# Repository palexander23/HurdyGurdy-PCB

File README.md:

# Electronic Hurdy Gurdy PCB

This repository contains PCB design files, that will go towards the eventual creation of an electronic Hurdy Gurdy.

This is a stand-in README that will likely be rewritten once the project starts taking off.

I do not intend this project to be seen widely, it's just a place for me to keep stuff.

This project was heavily inspired by the [Digi-Gurdy](https://hackaday.io/project/165251-the-digi-gurdy-and-diginerdygurdy) and much of the mechanical design for my instrument will likely be drawn from there.

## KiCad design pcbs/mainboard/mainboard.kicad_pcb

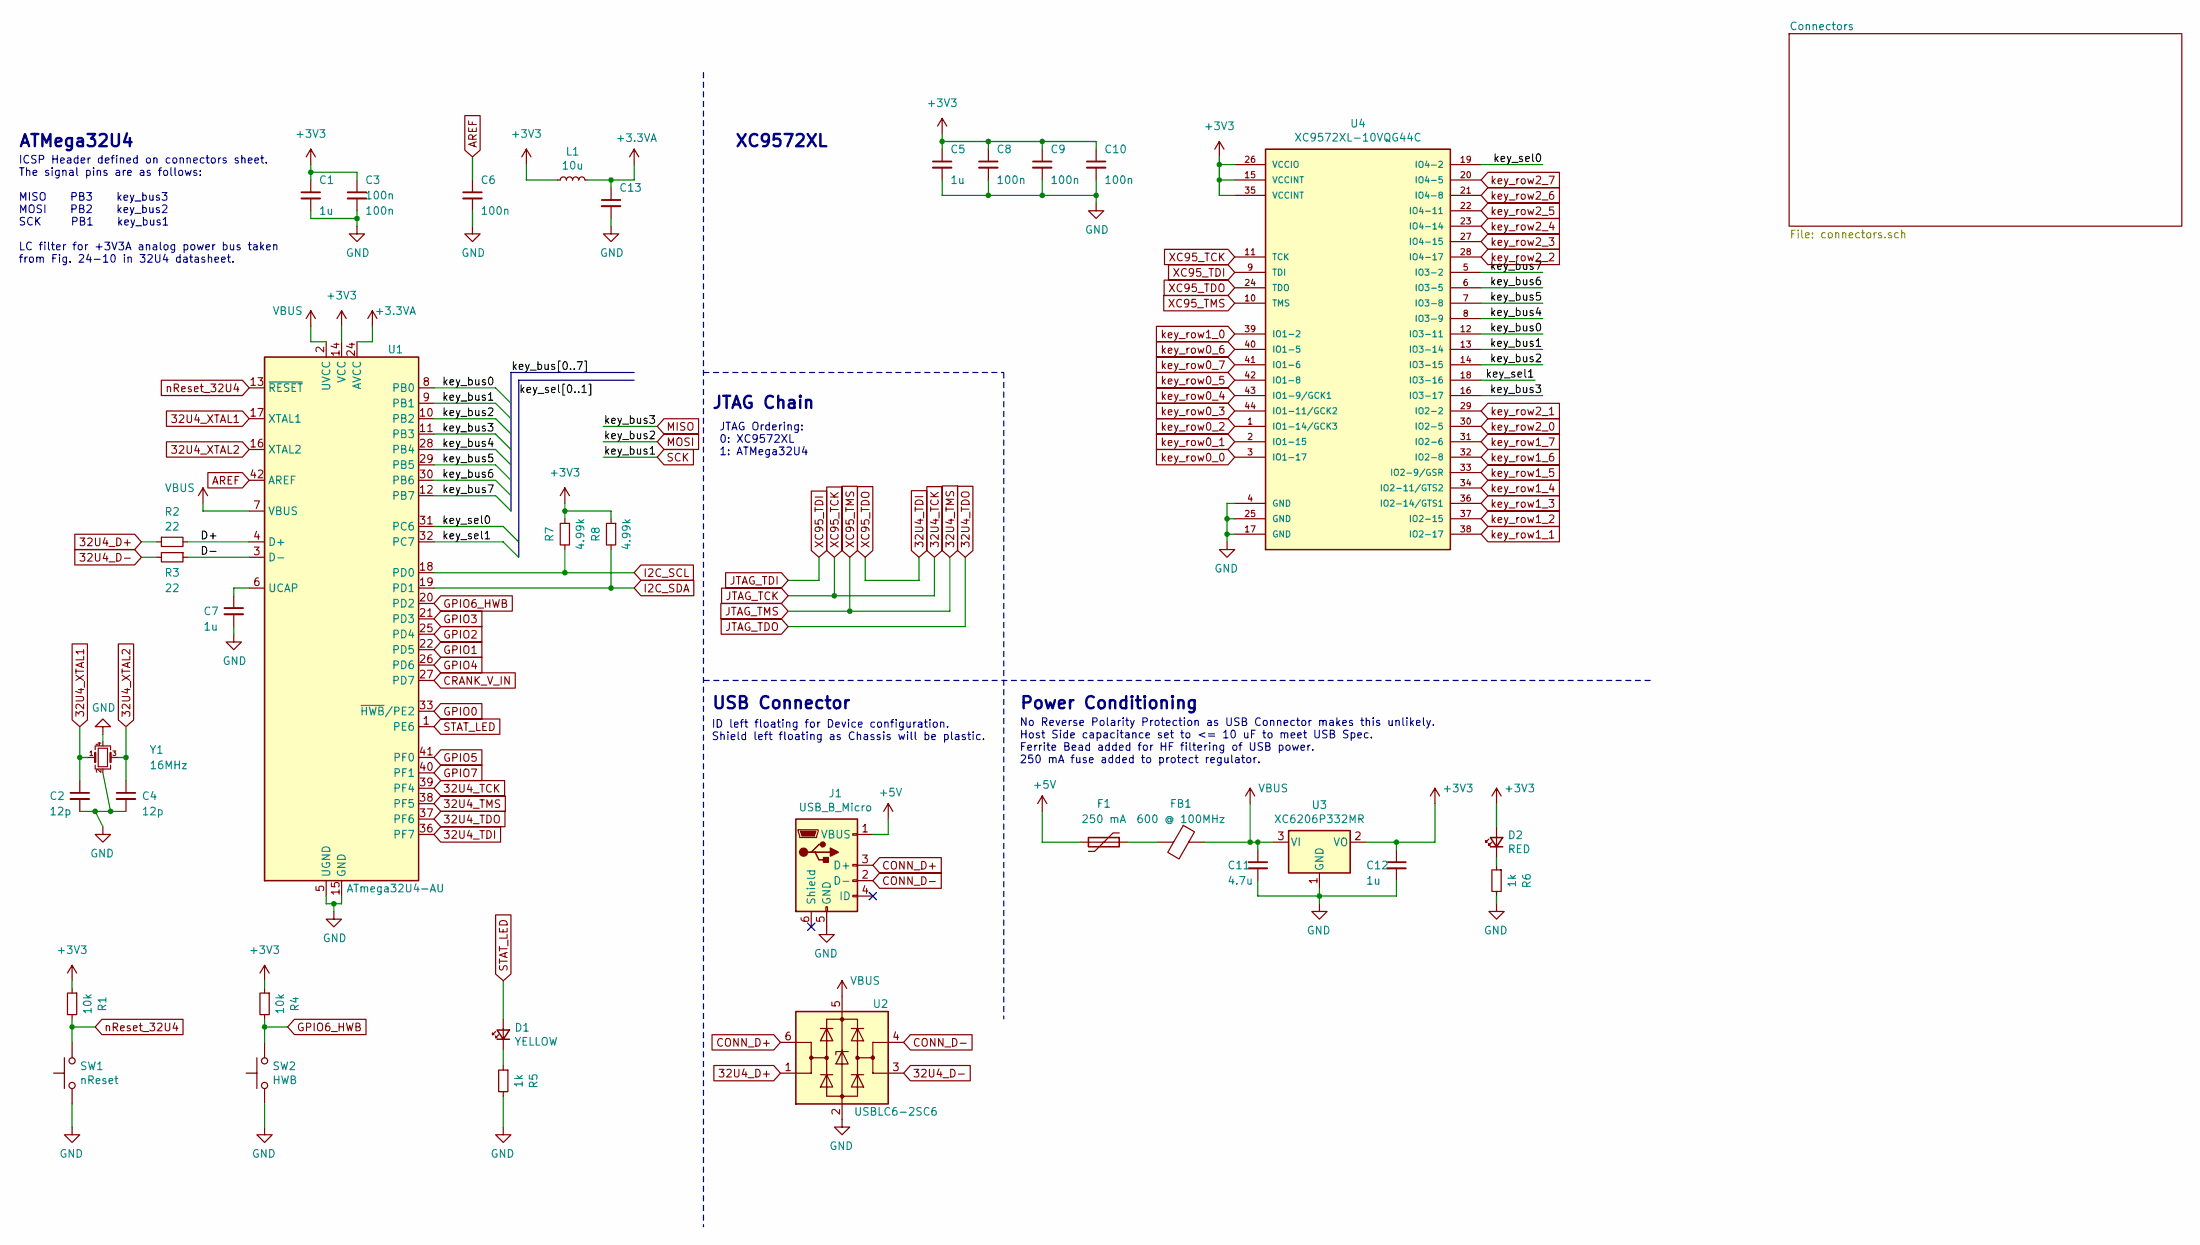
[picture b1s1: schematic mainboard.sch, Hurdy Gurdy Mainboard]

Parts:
C1, C5, C7, C12: 1u; C_0603_1608Metric; JLCPCB Part # C15849
C2, C4: 12p; C_0603_1608Metric; JLCPCB Part # C38523
C3, C6, C8, C9, C10, C13: 100n; C_0603_1608Metric; JLCPCB Part # C14663
C11: 4.7u; C_0603_1608Metric; JLCPCB Part # C19666
D1: YELLOW; LED_0603_1608Metric; JLCPCB Part # C72038
D2: RED; LED_0603_1608Metric; JLCPCB Part # C2286
F1: 250 mA; Fuse_1206_3216Metric; JLCPCB Part # C369154
FB1: 600 @ 100MHz; L_0805_2012Metric; JLCPCB Part # C1017
J1: USB_B_Micro; USB_Micro-B_Amphenol_10103594-0001LF_Horizontal
L1: 10u; L_1206_3216Metric; JLCPCB Part # C1051
R1, R4: 10k; R_0603_1608Metric; JLCPCB Part # C25804
R2, R3: 22; R_0603_1608Metric; JLCPCB Part # C23345
R5, R6: 1k; R_0603_1608Metric; JLCPCB Part # C21190
R7, R8: 4.99k; R_0603_1608Metric; JLCPCB Part # C23046
SW1: nReset; SW_PUSH_6mm
SW2: HWB; SW_PUSH_6mm
U1: ATmega32U4-AU; TQFP-44_10x10mm_P0.8mm; JLCPCB Part # C44854
U2: USBLC6-2SC6; SOT-23-6; JLCPCB Part # C2827654
U3: XC6206P332MR; SOT-23; JLCPCB Part # C5446
U4: XC9572XL-10VQG44C; VQFP-44; JLCPCB Part # C569042
Y1: 16MHz; Crystal_SMD_3225-4Pin_3.2x2.5mm; JLCPCB Part # C13738

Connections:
32U4_D+: R2.1, U2.1 (I/O1)
32U4_D-: R3.2, U2.3 (I/O2)
32U4_TCK: U1.39 (PF4), U4.11 (TCK); also elsewhere on the board
32U4_TDI: U1.36 (PF7), U4.24 (TDO)
32U4_TDO: U1.37 (PF6); also elsewhere on the board
32U4_TMS: U1.38 (PF5), U4.10 (TMS); also elsewhere on the board
32U4_XTAL1: C2.1, U1.17 (XTAL1), Y1.1
32U4_XTAL2: C4.1, U1.16 (XTAL2), Y1.3
+3.3VA: C13.1, L1.2, U1.24 (AVCC), U1.44 (AVCC)
+3V3: C1.1, C3.1, C5.1, C8.1, C9.1, C10.1, C12.1, D2.2 (A), L1.1, R1.1, R4.1, R7.1, R8.1, U1.14 (VCC), U1.34 (VCC), U3.2 (VO), U4.15 (VCCINT), U4.26 (VCCIO), U4.35 (VCCINT); also elsewhere on the board
+5V: F1.2, J1.1 (VBUS)
/D+: R2.2, U1.4 (D+)
/D-: R3.1, U1.3 (D-)
/key_bus0: U1.8 (PB0), U4.12 (IO3-11)
/key_bus4: U1.28 (PB4), U4.8 (IO3-9)
/key_bus5: U1.29 (PB5), U4.7 (IO3-8)
/key_bus6: U1.30 (PB6), U4.6 (IO3-5)
/key_bus7: U1.12 (PB7), U4.5 (IO3-2)
/key_sel0: U1.31 (PC6), U4.19 (IO4-2)
/key_sel1: U1.32 (PC7), U4.18 (IO3-16)
AREF: C6.1, U1.42 (AREF)
CONN_D+: J1.3 (D+), U2.6 (I/O1)
CONN_D-: J1.2 (D-), U2.4 (I/O2)
CRANK_V_IN: U1.27 (PD7); also elsewhere on the board
GND: C1.2, C2.2, C3.2, C4.2, C5.2, C6.2, C7.2, C8.2, C9.2, C10.2, C11.2, C12.2, C13.2, J1.5 (GND), R5.2, R6.2, SW1.1, SW2.1, U1.5 (UGND), U1.15 (GND), U1.23 (GND), U1.35 (GND), U1.43 (GND), U2.2 (GND), U3.1 (GND), U4.4 (GND), U4.17 (GND), U4.25 (GND), Y1.2, Y1.4; also elsewhere on the board
GPIO0: U1.33 (~HWB~/PE2); also elsewhere on the board
GPIO1: U1.22 (PD5); also elsewhere on the board
GPIO2: U1.25 (PD4); also elsewhere on the board
GPIO3: U1.21 (PD3); also elsewhere on the board
GPIO4: U1.26 (PD6); also elsewhere on the board
GPIO5: U1.41 (PF0); also elsewhere on the board
GPIO6_HWB: R4.2, SW2.2, U1.20 (PD2); also elsewhere on the board
GPIO7: U1.40 (PF1); also elsewhere on the board
I2C_SCL: R7.2, U1.18 (PD0); also elsewhere on the board
I2C_SDA: R8.2, U1.19 (PD1); also elsewhere on the board
JTAG_TDI: U4.9 (TDI); also elsewhere on the board
MISO: U1.11 (PB3), U4.16 (IO3-17); also elsewhere on the board
MOSI: U1.10 (PB2), U4.14 (IO3-15); also elsewhere on the board
unnamed: C7.1, U1.6 (UCAP)
unnamed: D1.1 (K), R5.1
unnamed: D2.1 (K), R6.1
unnamed: F1.1, FB1.2
SCK: U1.9 (PB1), U4.13 (IO3-14); also elsewhere on the board
STAT_LED: D1.2 (A), U1.1 (PE6); also elsewhere on the board
VBUS: C11.1, FB1.1, U1.2 (UVCC), U1.7 (VBUS), U2.5 (VBUS), U3.3 (VI); also elsewhere on the board
key_row0_0: U4.3 (IO1-17); also elsewhere on the board
key_row0_1: U4.2 (IO1-15); also elsewhere on the board
key_row0_2: U4.1 (IO1-14/GCK3); also elsewhere on the board
key_row0_3: U4.44 (IO1-11/GCK2); also elsewhere on the board
key_row0_4: U4.43 (IO1-9/GCK1); also elsewhere on the board
key_row0_5: U4.42 (IO1-8); also elsewhere on the board
key_row0_6: U4.40 (IO1-5); also elsewhere on the board
key_row0_7: U4.41 (IO1-6); also elsewhere on the board
key_row1_0: U4.39 (IO1-2); also elsewhere on the board
key_row1_1: U4.38 (IO2-17); also elsewhere on the board
key_row1_2: U4.37 (IO2-15); also elsewhere on the board
key_row1_3: U4.36 (IO2-14/GTS1); also elsewhere on the board
key_row1_4: U4.34 (IO2-11/GTS2); also elsewhere on the board
key_row1_5: U4.33 (IO2-9/GSR); also elsewhere on the board
key_row1_6: U4.32 (IO2-8); also elsewhere on the board
key_row1_7: U4.31 (IO2-6); also elsewhere on the board
key_row2_0: U4.30 (IO2-5); also elsewhere on the board
key_row2_1: U4.29 (IO2-2); also elsewhere on the board
key_row2_2: U4.28 (IO4-17); also elsewhere on the board
key_row2_3: U4.27 (IO4-15); also elsewhere on the board
key_row2_4: U4.23 (IO4-14); also elsewhere on the board
key_row2_5: U4.22 (IO4-11); also elsewhere on the board
key_row2_6: U4.21 (IO4-8); also elsewhere on the board
key_row2_7: U4.20 (IO4-5); also elsewhere on the board
nReset_32U4: R1.2, SW1.2, U1.13 (~RESET); also elsewhere on the board

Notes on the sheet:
ATMega32U4
XC9572XL
JTAG Chain
JTAG Ordering: 0: XC9572XL 1: ATMega32U4
USB Connector
ID left floating for Device configuration. Shield left floating as Chassis will be plastic.
Power Conditioning
No Reverse Polarity Protection as USB Connector makes this unlikely. Host Side capacitance set to <= 10 uF to meet USB Spec. Ferrite Bead added for HF filtering of USB power. 250 mA fuse added to protect regulator.
ICSP Header defined on connectors sheet. The signal pins are as follows: MISO PB3 key_bus3 MOSI PB2 key_bus2 SCK PB1 key_bus1 LC filter for +3V3A analog power bus taken from Fig. 24-10 in 32U4 datasheet.

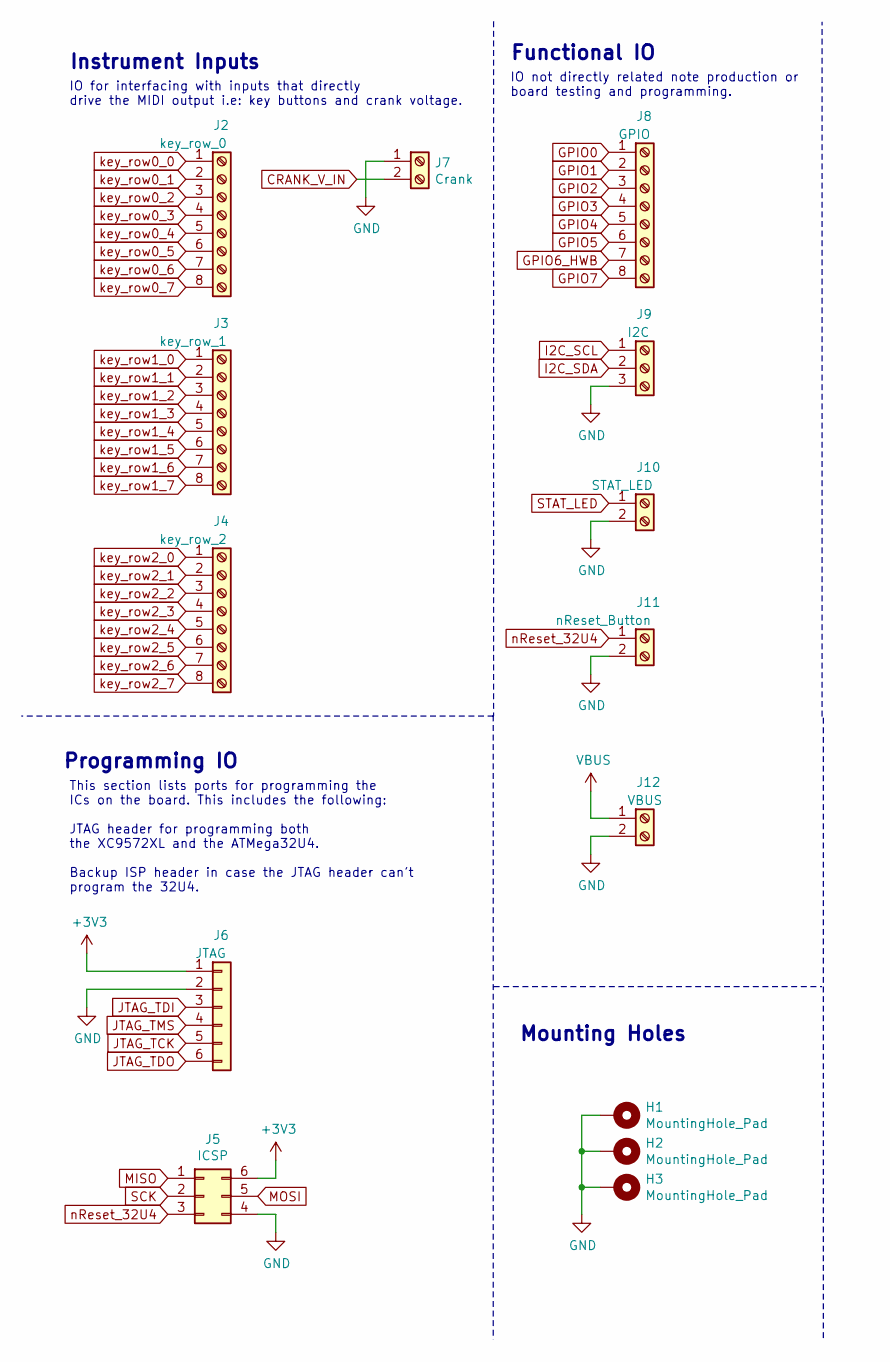
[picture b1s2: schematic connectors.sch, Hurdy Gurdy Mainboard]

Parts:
H1, H2, H3: MountingHole_Pad; MountingHole_3.2mm_M3_Pad_Via
J2: key_row_0; TerminalBlock_Phoenix_MKDS-1,5-8-5.08_1x08_P5.08mm_Horizont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
J3: key_row_1; TerminalBlock_Phoenix_MKDS-1,5-8-5.08_1x08_P5.08mm_Horizont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
J4: key_row_2; TerminalBlock_Phoenix_MKDS-1,5-8-5.08_1x08_P5.08mm_Horizont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
J5: ICSP; PinHeader_2x03_P2.54mm_Vertical
J6: JTAG; PinHeader_1x06_P2.54mm_Vertical
J7: Crank; TerminalBlock_Phoenix_MKDS-1,5-2-5.08_1x02_P5.08mm_Horizont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
J8: GPIO; TerminalBlock_Phoenix_MKDS-1,5-8-5.08_1x08_P5.08mm_Horizont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
J9: I2C; TerminalBlock_Phoenix_MKDS-1,5-3-5.08_1x03_P5.08mm_Horizont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
J10: STAT_LED; TerminalBlock_Phoenix_MKDS-1,5-2-5.08_1x02_P5.08mm_Horizont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
J11: nReset_Button; TerminalBlock_Phoenix_MKDS-1,5-2-5.08_1x02_P5.08mm_Horizont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
J12: VBUS; TerminalBlock_Phoenix_MKDS-1,5-2-5.08_1x02_P5.08mm_Horizont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

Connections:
32U4_TCK: J6.5; also elsewhere on the board
32U4_TDO: J6.6; also elsewhere on the board
32U4_TMS: J6.4; also elsewhere on the board
+3V3: J5.6, J6.1; also elsewhere on the board
CRANK_V_IN: J7.2; also elsewhere on the board
GND: H1.1, H2.1, H3.1, J5.4, J6.2, J7.1, J9.3, J10.2, J11.2, J12.2; also elsewhere on the board
GPIO0: J8.1; also elsewhere on the board
GPIO1: J8.2; also elsewhere on the board
GPIO2: J8.3; also elsewhere on the board
GPIO3: J8.4; also elsewhere on the board
GPIO4: J8.5; also elsewhere on the board
GPIO5: J8.6; also elsewhere on the board
GPIO6_HWB: J8.7; also elsewhere on the board
GPIO7: J8.8; also elsewhere on the board
I2C_SCL: J9.1; also elsewhere on the board
I2C_SDA: J9.2; also elsewhere on the board
JTAG_TDI: J6.3; also elsewhere on the board
MISO: J5.1; also elsewhere on the board
MOSI: J5.5; also elsewhere on the board
SCK: J5.2; also elsewhere on the board
STAT_LED: J10.1; also elsewhere on the board
VBUS: J12.1; also elsewhere on the board
key_row0_0: J2.1; also elsewhere on the board
key_row0_1: J2.2; also elsewhere on the board
key_row0_2: J2.3; also elsewhere on the board
key_row0_3: J2.4; also elsewhere on the board
key_row0_4: J2.5; also elsewhere on the board
key_row0_5: J2.6; also elsewhere on the board
key_row0_6: J2.7; also elsewhere on the board
key_row0_7: J2.8; also elsewhere on the board
key_row1_0: J3.1; also elsewhere on the board
key_row1_1: J3.2; also elsewhere on the board
key_row1_2: J3.3; also elsewhere on the board
key_row1_3: J3.4; also elsewhere on the board
key_row1_4: J3.5; also elsewhere on the board
key_row1_5: J3.6; also elsewhere on the board
key_row1_6: J3.7; also elsewhere on the board
key_row1_7: J3.8; also elsewhere on the board
key_row2_0: J4.1; also elsewhere on the board
key_row2_1: J4.2; also elsewhere on the board
key_row2_2: J4.3; also elsewhere on the board
key_row2_3: J4.4; also elsewhere on the board
key_row2_4: J4.5; also elsewhere on the board
key_row2_5: J4.6; also elsewhere on the board
key_row2_6: J4.7; also elsewhere on the board
key_row2_7: J4.8; also elsewhere on the board
nReset_32U4: J5.3, J11.1; also elsewhere on the board

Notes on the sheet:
Instrument Inputs
IO for interfacing with inputs that directly drive the MIDI output i.e: key buttons and crank voltage.
Functional IO
IO not directly related note production or board testing and programming.
Programming IO
This section lists ports for programming the ICs on the board. This includes the following: JTAG header for programming both the XC9572XL and the ATMega32U4. Backup ISP header in case the JTAG header can't program the 32U4.
Mounting Holes

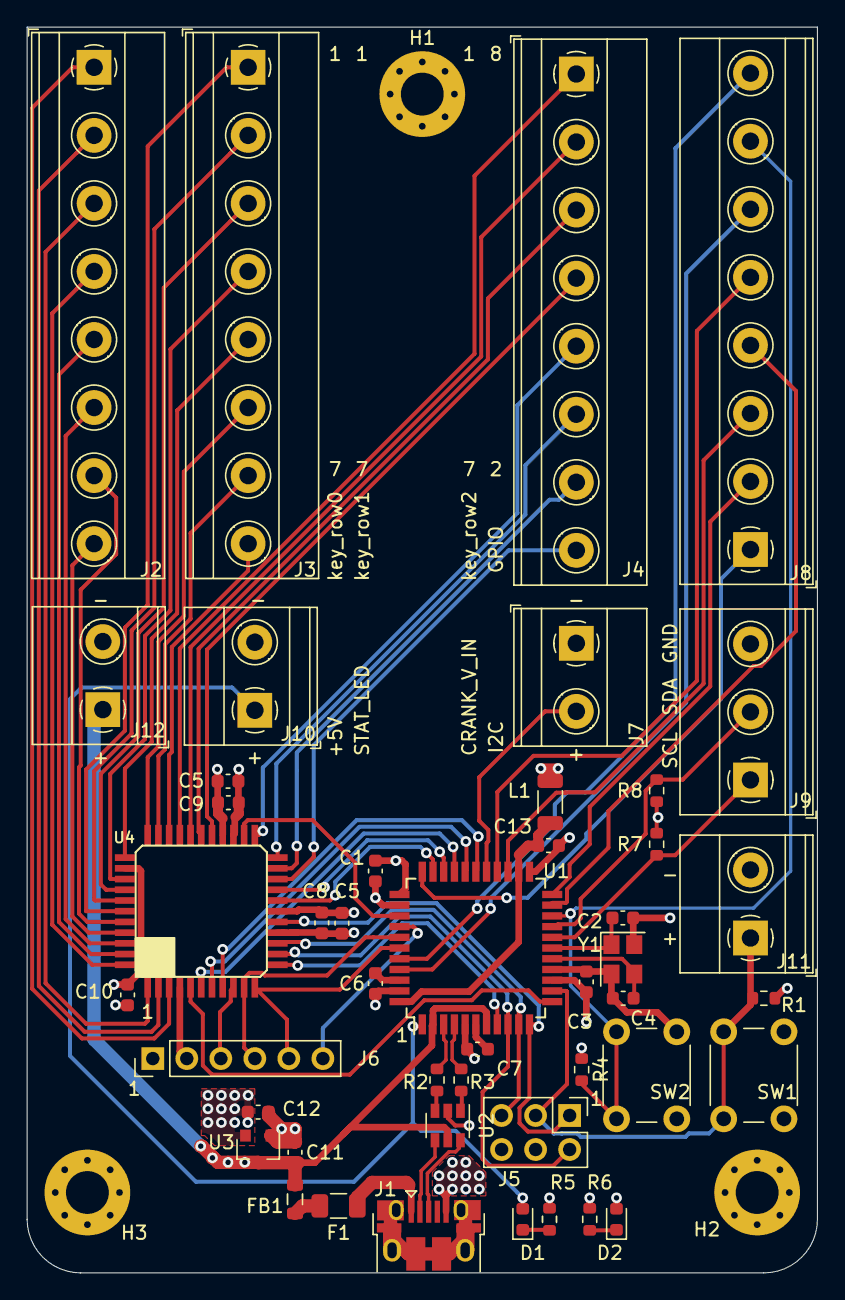
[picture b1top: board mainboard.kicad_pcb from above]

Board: 4 copper layers, 59.0 x 93.0 mm, 49 parts (0 on the bottom side), 70 nets.

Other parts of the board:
C5#2: 100n; C_0603_1608Metric

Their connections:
+3V3: C5#2.1; also elsewhere on the board
GND: C5#2.2; also elsewhere on the board

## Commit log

2021-09-03 Initial commit
    Add simple, stand-in README.
    Add block diagram for the main electronics.
2021-09-13 Add WIP mainboard schemetic: Power, MCU, USB
    Add Schematic blocs for:
    * ATMega32U4 MCU
    * XC9572XL CPLD for key management
    * JTAG Chain
    * Power Regulation/Conditioning
    * USB Input/ESD Protection
2021-09-17 Add completed schematic with footprints
    Add completed schematic with connectors for all IO and programming
    devices.
    Connectors laid out on a separate sheet.
    DRC check completed.
    One rule left unfulfilled resulting from KiCAD not recognising when
    a power signal has run all but undisturbed through a power filter.
2021-09-22 Add 3V3A filter and JLC Part numbers
    Add a single stage LC filter to the ADC power input.
    Design taken from Fig. 24-10 in 32U4 datasheet.
    Add JLC part numbers for all SMD parts.
    XC95 part was out of stock at time of commit.
2021-09-22 Add mounting holes and fix button footprint
    Replace button footprint with one which matches the symbol.
2021-09-22 Add VBUS screw terminal
    Add VBUS screw terminal to allow future subsystems to draw current
    from the USB connection, bypassing the small 3V3 regulator.
2021-09-22 Edit bypass capacitors, add JLC part for LDO
    Both 32U4 and XC95 now bave 1uF bulk capacitor as well as a 100nF
    for each VCC/GND pair.
2021-09-24 Add first draft of mainboard layout
    Change pinout of XC95 to better link to the key_row screw terminals.
    Change ordering of some signals on screw terminals and JTAG header
    to allow more sensible routing.
    Revise mounting hole scheme to only place one between the two rows
    of terminal blocks rather than at each corner on the top.
2021-09-24 Add first draft of mainboard routing
2021-09-26 Improve routing around 32U4
    Move some pin assignments round on the 32U4 to simplify routing
    to the lower-priority IO.
2021-09-26 Fix vias placed under SMD pads
    Move vias out from underneath SMD pads to prevent solder paste
    being sucked into them during manufacture.
    Redo power layout to accomadate large areas of vias to power planes.
2021-09-26 Add useful/readabhle silkscreen
    Swap pins on CRANK_V_IN terminal block to shorten track
    and match the polarity of other +/- terminal blocks.
2021-09-27 Move H2, H3 up to ease USB port chassis placement
    Move mounting holes H2 and H3 up a few mm to allow the USB port to
    allow the USB port to be placed as close to the edge of the
    chassis as possible.
2021-09-27 Add copper pour keepout under crystal
2022-01-30 Update README to match repo rename
    Update README to match the repo rebranding for PCBs
